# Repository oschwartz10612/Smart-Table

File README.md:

# Smart-Table

A table that moves in the X axis.

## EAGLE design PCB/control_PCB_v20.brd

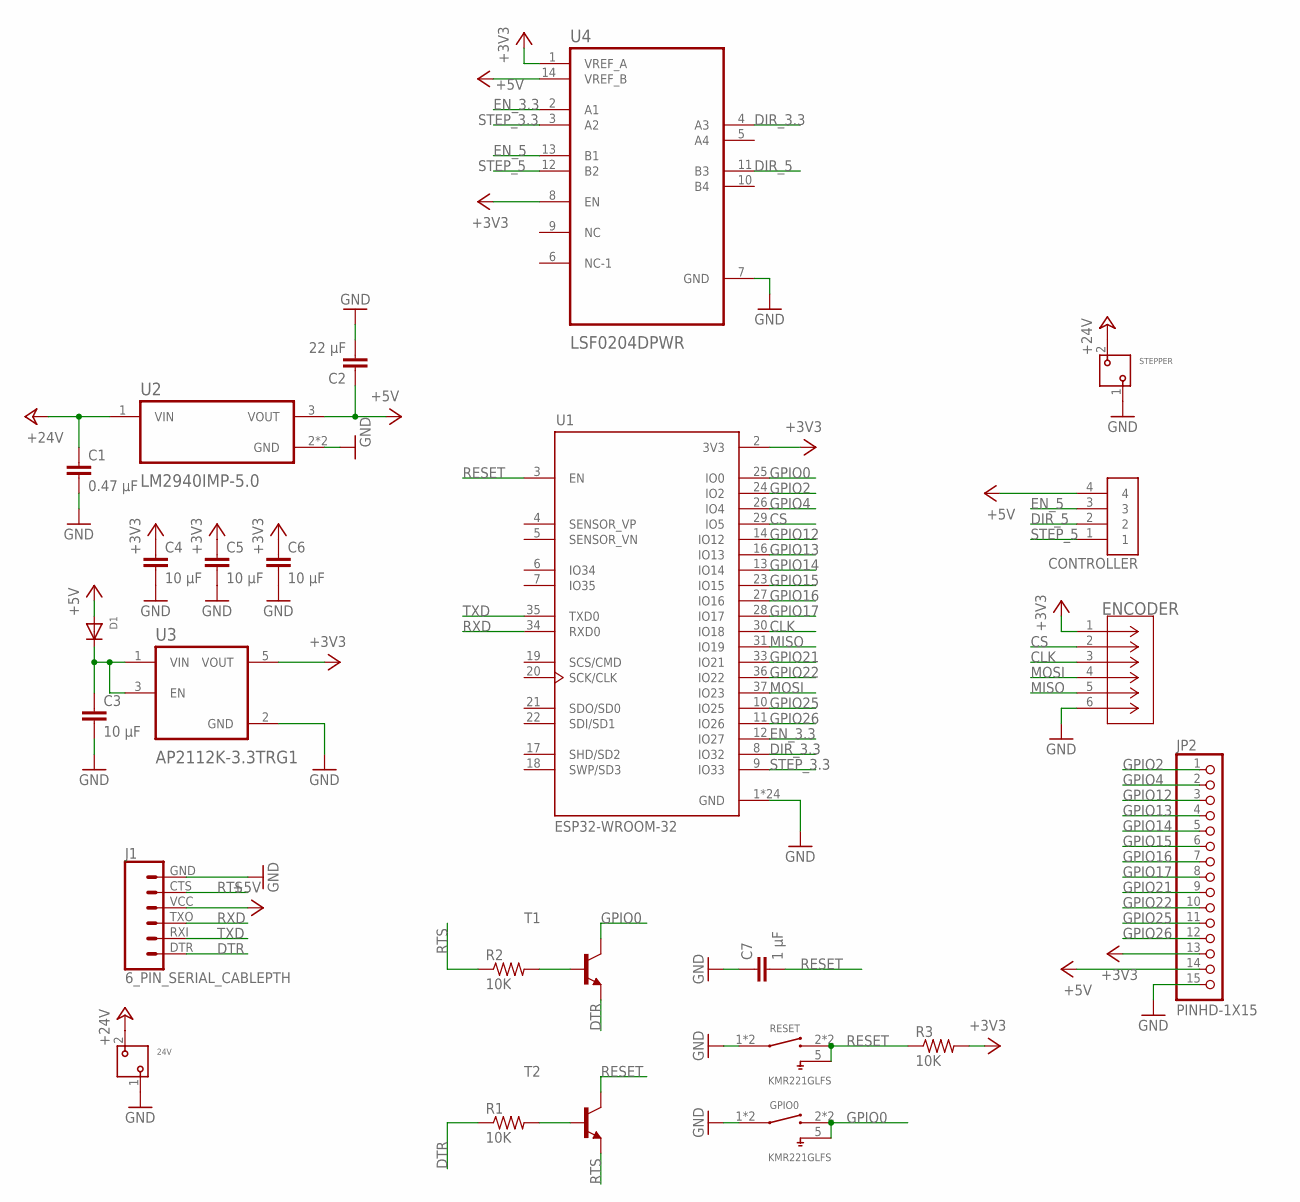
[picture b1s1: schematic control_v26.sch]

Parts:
24V: 691412320002
C1: 0.47 µF; C0805
C2: 22 µF; C0805
C3, C4, C5, C6: 10 µF; C0805
C7: 1 µF; C0805
CONTROLLER: B4B-XH-A(LF)(SN); JST_B4B-XH-A(LF)(SN)
D1: DIODESOD-123; SOD-123
ENCODER: B6B-XH-A_(LF)(SN); CONN_B6B-XH-A_JST
GPIO0: KMR221GLFS; SW_KMR221GLFS
J1: 6_PIN_SERIAL_CABLEPTH; FTDI_BASIC
JP2: PINHD-1X15; 1X15
R1, R2, R3: 10K; R0805
RESET: KMR221GLFS; SW_KMR221GLFS
STEPPER: 691412320002
T1, T2: MMBT2222ALT1-NPN-SOT23-BEC; SOT23-BEC
U1: ESP32-WROOM-32; MODULE_ESP32-WROOM-32
U2: LM2940IMP-5.0; SOT230P700X180-4N
U3: AP2112K-3.3TRG1; SOT95P285X140-5N
U4: LSF0204DPWR; SOP65P640X120-14N

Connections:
+3V3: C4.1, C5.1, C6.1, ENCODER.1, JP2.13, R3.2, U1.2 (3V3), U3.5 (VOUT), U4.1 (VREF_A), U4.8 (EN)
+5V: C2.1, CONTROLLER.4, D1.A, J1.VCC (4), JP2.14, U2.3 (VOUT), U4.14 (VREF_B)
+24V: 24V.2, C1.1, STEPPER.2, U2.1 (VIN)
CLK: ENCODER.3, U1.30 (IO18)
CS: ENCODER.2, U1.29 (IO5)
DIR_3.3: U1.8 (IO32), U4.4 (A3)
DIR_5: CONTROLLER.2, U4.11 (B3)
DTR: J1.DTR (1), R1.1, T1.E
EN_3.3: U1.12 (IO27), U4.2 (A1)
EN_5: CONTROLLER.3, U4.13 (B1)
GND: 24V.1, C1.2, C2.2, C3.2, C4.2, C5.2, C6.2, C7.1, ENCODER.6, GPIO0.1, GPIO0.4 (1), J1.GND (6), JP2.15, RESET.1, RESET.4 (1), STEPPER.1, U1.1 (GND), U1.15 (GND), U1.38 (GND), U1.39_1 (GND), U1.39_2 (GND), U1.39_3 (GND), U1.39_4 (GND), U1.39_5 (GND), U1.39_6 (GND), U1.39_7 (GND), U1.39_8 (GND), U1.39_9 (GND), U1.39_10 (GND), U1.39_11 (GND), U1.39_12 (GND), U1.39_13 (GND), U1.39_14 (GND), U1.39_15 (GND), U1.39_16 (GND), U1.39_17 (GND), U1.39_18 (GND), U1.39_19 (GND), U1.39_20 (GND), U1.39_21 (GND), U2.2 (GND), U2.4 (GND), U3.2 (GND), U4.7 (GND)
GPIO0: GPIO0.2 (3), GPIO0.3, GPIO0.5, T1.C, U1.25 (IO0)
GPIO2: JP2.1, U1.24 (IO2)
GPIO4: JP2.2, U1.26 (IO4)
GPIO12: JP2.3, U1.14 (IO12)
GPIO13: JP2.4, U1.16 (IO13)
GPIO14: JP2.5, U1.13 (IO14)
GPIO15: JP2.6, U1.23 (IO15)
GPIO16: JP2.7, U1.27 (IO16)
GPIO17: JP2.8, U1.28 (IO17)
GPIO21: JP2.9, U1.33 (IO21)
GPIO22: JP2.10, U1.36 (IO22)
GPIO25: JP2.11, U1.10 (IO25)
GPIO26: JP2.12, U1.11 (IO26)
MISO: ENCODER.5, U1.31 (IO19)
MOSI: ENCODER.4, U1.37 (IO23)
unnamed: C3.1, D1.C, U3.1 (VIN), U3.3 (EN)
unnamed: R1.2, T2.B
unnamed: R2.2, T1.B
RESET: C7.2, R3.1, RESET.2 (3), RESET.3, RESET.5, T2.C, U1.3 (EN)
RTS: J1.CTS (5), R2.1, T2.E
RXD: J1.TXO (3), U1.34 (RXD0)
STEP_3.3: U1.9 (IO33), U4.3 (A2)
STEP_5: CONTROLLER.1, U4.12 (B2)
TXD: J1.RXI (2), U1.35 (TXD0)

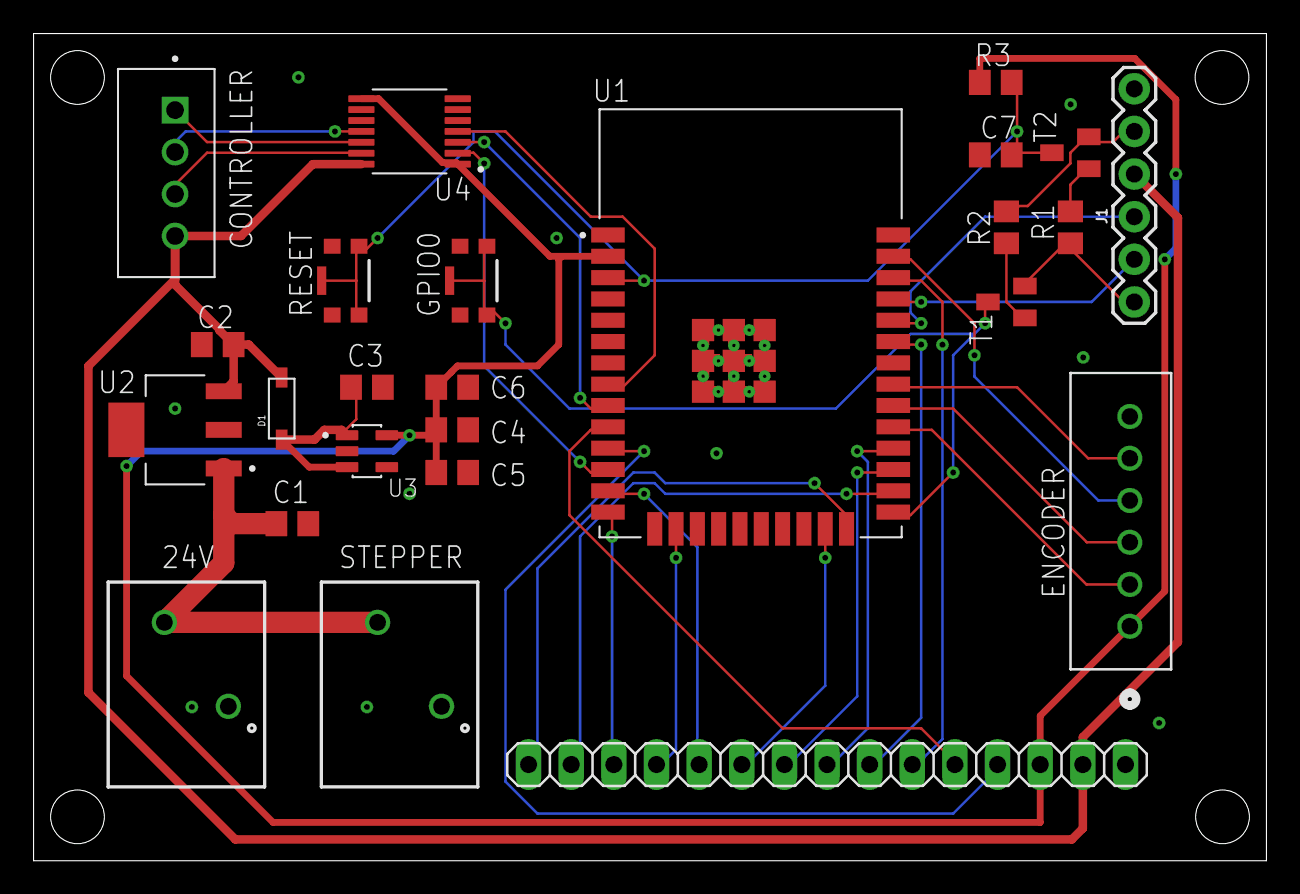
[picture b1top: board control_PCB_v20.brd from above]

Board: 2 copper layers, 73.5 x 49.3 mm, 25 parts (0 on the bottom side), 35 nets.

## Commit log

2020-08-22 Setup enviroment
2020-08-22 Added basic PID
2020-08-22 Clean up pid
2020-08-22 strcmp payload in callback
2020-08-22 MQTT callback pointers
2020-08-22 Add PCB
2020-08-23 Added stepper control and mapping
2020-08-24 Successfull upload
2020-08-30 This damn AS5048A
2020-09-01 Fix AS5048A issue
2020-09-02 Added debug, smoothing, velocity
2020-09-03 Stepper abs pos calc by stepper velocuty
2020-09-03 Set zero at setup
2020-09-05 Tranzition to PID
2020-09-06 PID encoder working basic
2020-09-07 Stop and save pos when at setpoint
2020-09-07 Fix kernel panic
2020-09-07 Ready for table insertion
2020-09-07 Adjustments for table
2020-09-08 Polished with new rack (works better)
2020-09-08 Timeout delay
2020-09-11 Added state persistance
2020-09-13 Added defines for vals
2020-09-13 Cleanup
2020-09-13 Change to vTask Dekay
2020-09-13 Trying to reduce space
    Explict var defs
2020-09-13 Fix drift issue
2020-09-13 Add timeout counter
2020-09-13 Fix dynaic correction drifting
2020-09-13 Production run 2 code
2020-09-13 Fix SLEEP_TIMEOUT
2020-09-13 Remove DS_store
2020-09-15 Only calc absStepperPos when target is not reached
2020-09-18 Chang dlay
2020-09-18 AS5048A lib #ifdef DEBUG replacement
2020-09-18 Remove .DS_Store
2020-09-20 Reset smoothing in setup and enable stepper
2020-09-21 Reset smooth
2020-09-23 Slight originization
2020-09-23 Decrese costing delay to 150
2020-10-03 Cleanup code
2020-10-03 More code cleanup
2020-10-04 Increse up to 1000
2020-10-11 Value changes and cleanup
2020-10-11 Finished tuning
2020-10-11 Removed smoothing
2020-10-11 Tweaks - network not working when enabled?
2020-10-19 Initialize motion after network
    Print time difference
2020-10-19 Fixed network issue and tuned activation val
2020-11-08 Uplaod
2020-11-09 Remove unessasry git files
2020-11-11 Fix wifi disconnect
2020-11-11 Fix serial debug issue
2020-11-12 Small table fixes
2020-11-12 Added more logs mqtt
2020-11-12 Removed string useage
2020-11-12 Added termination to string
2020-11-12 WOrking on commands feature
2020-11-12 Add more logs and change topics
2021-01-01 Change vals
2021-01-01 Move stepper pulses into isr
2021-01-14 Remote preferences
2023-05-27 Remove network for now

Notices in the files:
parts and their libraries:
SparkFun-Connectors: Licensing: Creative Commons ShareAlike 4.0 International - https://creativecommons.org/licenses/by-sa/4.0
COPYRIGHT: Copyright (C) 2018 Accelerated Designs. All rights reserved
